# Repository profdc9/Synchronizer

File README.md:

# Synchronizer

Keep a mechanical pendulum clock on time by disciplining it to NTP or GPS —
**without modifying the clock in any way.**

The device sits behind the clock. Two coils reach through the back of the
case: one listens to the pendulum, the other nudges it. Nothing is glued to
the bob, nothing is drilled, nothing is tapped into the movement. Take the
device away and you have an ordinary pendulum clock again.

## How it works

A pendulum clock keeps time by counting swings. If the pendulum runs a
little fast or slow — and they all do, with temperature, with the mainspring
unwinding, with the barometric pressure — the hands drift. The usual fix is
to adjust the rating nut and accept a few seconds a day.

This device measures the pendulum against an accurate reference and gives it
a very small push, at the right moment, to hold it on time.

### Sensing the pendulum

The **sense coil** is an air-cored coil of many turns. It sits behind the
case, near one end of the pendulum's travel, and forms a parallel resonant
tank with C3 (in parallel with C4, an optional trim position). The firmware
drives that tank at its resonant frequency with a square wave.

When the bob swings past, it changes the coil's inductance and loads it with
eddy-current loss. Either way the tank is pulled off resonance, its
impedance falls, and the voltage across it drops. An LM358 amplifies that,
and the result is read two ways: as the raw waveform, and through an
envelope detector that turns it into a slow bump. The bump is the bob going
past.

Arrival time is taken as the **midpoint between the two threshold
crossings**, not the peak. At the end of its travel the bob is nearly
stationary, so the bump is broad and its peak is poorly localised — but the
two flanks are steep and symmetric about the turning point.

### Nudging the pendulum

The **drive coil** is wound on a soft iron core and sits at the other end of
the swing. Energising it attracts the bob's steel backing. It can only pull,
never push, so correction is entirely a matter of *when*:

- pulse **just before** the bob arrives → it gets there sooner → **the clock
  advances**
- pulse **just after** it turns and starts back → it is held a moment
  longer → **the clock retards**

The pushes needed are tiny. On the development clock, correcting 11 s/day
works out to about **113 microseconds of retard per swing** — far too little
to deliver as a pulse every swing. So the firmware accumulates the demand
and spends it whole: one short pulse every few dozen swings.

### Keeping time

A Raspberry Pi Pico W runs the whole thing, and serves a web interface for
everything else — status, calibration, tuning. Setting one up needs no
serial terminal and no app: a board with no network raises its own access
point, and joining it opens the setup form. Afterwards it answers at
`synchronizer.local` and advertises itself over DNS-SD, so there is no IP
address to hunt for. The page carries a console that runs the same command
line as the serial port, and the same thing is reachable from `curl` for
scripting or remote debugging.

It gets the time over Wi-Fi by NTP, and keeps a model of UTC that NTP
corrects in both phase *and* rate —
the RP2040's crystal is only good to around 30 ppm, which is 2.6 s/day, a
sizeable fraction of the error being removed. A GPS receiver can be wired to
the expansion header later.

## The hardware

A single board, 99 × 62 mm, all through-hole parts. It is deliberately
**single-sided** — every track is on the bottom copper, with no vias and no
jumpers — so it can be milled at home if need be, though the boards in the
photo were commercially made.

### Connections

| | |
|---|---|
| **J1** | +12 V input, screw terminal |
| **J4** | +12 V input, barrel jack (wired in parallel with J1) |
| **J3** | Sense coil, screw terminal |
| **J5** | Drive coil, screw terminal |
| **J2** | 14-pin expansion header |

J2 carries GPIO5–GPIO15 with three grounds, for a GPS receiver or anything
else. GPIO12 and GPIO13 are UART0 TX/RX, on pins 10 and 11.

### Circuit blocks

**Power.** 12 V in, a 7805 down to 5 V, then a 1N5819 Schottky (D1) feeding
the Pico's VBUS and the LM358's supply. The diode is what lets you plug in
USB without back-feeding the regulator.

**Tank drive.** GPIO2 → Q1 (2N3904) → Q2 (2N3906), which injects into the
sense tank through R5 from the 12 V rail. A square wave at resonance.

**Amplifier.** Two inverting LM358 stages, both with 100 kΩ feedback,
biased to about 1.5 V so they run from a single supply. The op-amp is
socketed.

The first stage is fed from the tank through C6, only 100 pF, so its
reactance — roughly 80 kΩ at 20 kHz — dominates the 10 kΩ input resistor.
That makes the stage a gentle high-pass of about ×1.3 at 20 kHz rising with
frequency, rather than a flat ×10. C6 is a light tap on the tank rather than
a load on it, and it also adds its own 100 pF to the tank's capacitance
alongside C3. The second stage is AC-coupled through C8 and does run at
about ×10.

**Detectors.** The amplified waveform goes to ADC1 through R20. It also goes
through R19 and C11 into a clamp-and-rectify envelope detector (D3, D4) with
C9 and R21 setting the decay, and that goes to ADC0. D7 and D8 clamp both
ADC inputs to 3V3; D5, D6 and D9 clamp the tank input.

**Drive.** GPIO4 → Q4 (2N3904) → pulls the gate of Q3, an IRF9540N P-channel
MOSFET, whose source sits on +12 V. **GPIO4 high energises the coil.** The
current runs through R6, a 10 Ω power resistor. D2 (UF4007) is the flyback
clamp across the coil, and R22 with C10 snubs the switching node. R17 and
R18 are unpopulated positions for damping the coils if you need it.

**R6's job is damping the drive circuit's oscillations, not setting a
current limit by design** — size it to the coil actually wound rather than
assuming the populated value. A lower-resistance coil wants a smaller R6, and
in many cases R6 can be 0 Ω outright; a higher-resistance coil can tolerate,
and may need, more damping.

> **A word of caution about R6.** The coil's DC resistance depends on what
> you wind, and R6 is in series with it across 12 V. A pulse left on could
> put several watts into that resistor. The firmware bounds every pulse
> three independent ways — a hard ceiling on width, a watchdog timer that
> drops the pin regardless of what the rest of the code believes, and a
> token bucket capping the long-run duty cycle — and the pin is driven low
> before anything else initialises. Keep those limits in mind before
> widening the default pulse.

### Pin assignments

| Signal | Pico | Function |
|---|---|---|
| `/OSCIL` | GPIO2 | tank drive, square wave at resonance |
| `/PULSE` | GPIO4 | drive coil; **high = coil energised** |
| `/AMPLITUDE` | GPIO26 / ADC0 | envelope detector output |
| `/OSC_SIGNAL` | GPIO27 / ADC1 | amplified tank waveform |

## Physical setup

<table>
<tr>
<td width="50%"></td>
<td width="50%"></td>
</tr>
<tr>
<td>The development clock — a 31-day mantel regulator. Neither coil touches
it; both stand free behind the case, reaching through the back wall.</td>
<td>The two coil holders assembled and wired to the board, placed at
opposite extremes of the pendulum's swing — the recommended default
geometry. Each stands on a 3D-printed platform with a ballast cup at its
base — filled here with cement — so it stays put on the shelf rather than
picking up the pendulum's own vibration.</td>
</tr>
<tr>
<td></td>
<td></td>
</tr>
<tr>
<td>The drive coil: a 50 mm × 35 mm, 500 N lifting electromagnet, 12 V at
about 250 mA, on its holder.</td>
<td>The sense coil, wound on its own form — the parallel resonant tank
described above.</td>
</tr>
</table>

Both holders are FreeCAD models, parametric in coil/magnet dimensions — see
`CAD/` below.

## The web interface

The device serves its own dashboard — no app, no cloud account, nothing to
install. These are from the clock above, running live.

At-a-glance status: the loop's lock state and uncorrected error, the clock's
measured swing rate, network and NTP health, the sense detector, and the
drive coil's per-direction pulse widths — all on one screen, live.

The uncorrected error over time, with advance and retard pulses marked where
they fired; the size of each NTP correction below it; and the chime
diagnostic showing what the hands should currently read.

The same command line as the serial port, in the browser — `STATUS` shown
here, but any command works, from `curl` or from this console.

## Repository layout

| | |
|---|---|
| `board/` | KiCad 7 project — schematic, PCB, gerbers, and a pcb2gcode setup for milling |
| `Code/synchronizer/` | Pico W firmware. See [its README](Code/synchronizer/README.md) for build and bring-up. |
| `CAD/` | FreeCAD models, parametric, plus their STLs. See [its README](CAD/README.md) for what each one is. |
| `Simulations/` | Qucs-S / ngspice models of the coil sensor and the coil pulser |

## Status

The board is built, the firmware runs the loop against the real clock shown
above, and it locks and holds it on time. Correction uses **KICK**: a
one-directional bang-bang scheme, no up-front gain measurement needed — it
fires a short pulse no more than once every few swings, only while the
error is on the side of zero that direction corrects, and stops once it
crosses back. An earlier design spent an accumulated phase error against a
measured "price per pulse" (`MEASURE`/`AUTH`); that path has been removed —
KICK needs no such calibration and has proven to be the simpler, working
approach.

Bring-up order, and the web interface, are in the
[firmware README](Code/synchronizer/README.md).

## Other clocks

Nothing in the firmware assumes a particular movement. Pendulum period,
escapement, gear ratio, coil placement and detector timing are all
configurable and stored in flash. The defaults describe the clock this was
developed against, and are only a starting point.

That clock is a 31-day wall clock about 40 cm tall. Measured from a
three-minute recording of its escapement:

- full swing period **0.857030 s** — nominally 6/7 s
- **8400 beats/hour**, 140 beats/min, **4200 full swings/hour**
- pendulum about **18.3 cm**
- runs roughly **11 s/day fast**
- **203 ms out of beat**, stably — the escapement releases at 0.678 of peak
  swing, where the bob still has 73% of its top speed, so it runs happily
  that way

Note that the bob only reaches each end of its travel once per full period,
so a coil at one extreme sees it 4200 times an hour, not 8400.

## Licence

The board carries **CC BY-SA 4.0** on its silkscreen, and the CAD models are
under the same licence; the full text is in
[`LICENSE-CC-BY-SA-4.0.txt`](LICENSE-CC-BY-SA-4.0.txt). The firmware sources
each carry a zlib-style permissive notice, and the full text is in
[`Code/synchronizer/LICENSE`](Code/synchronizer/LICENSE).

Daniel Marks

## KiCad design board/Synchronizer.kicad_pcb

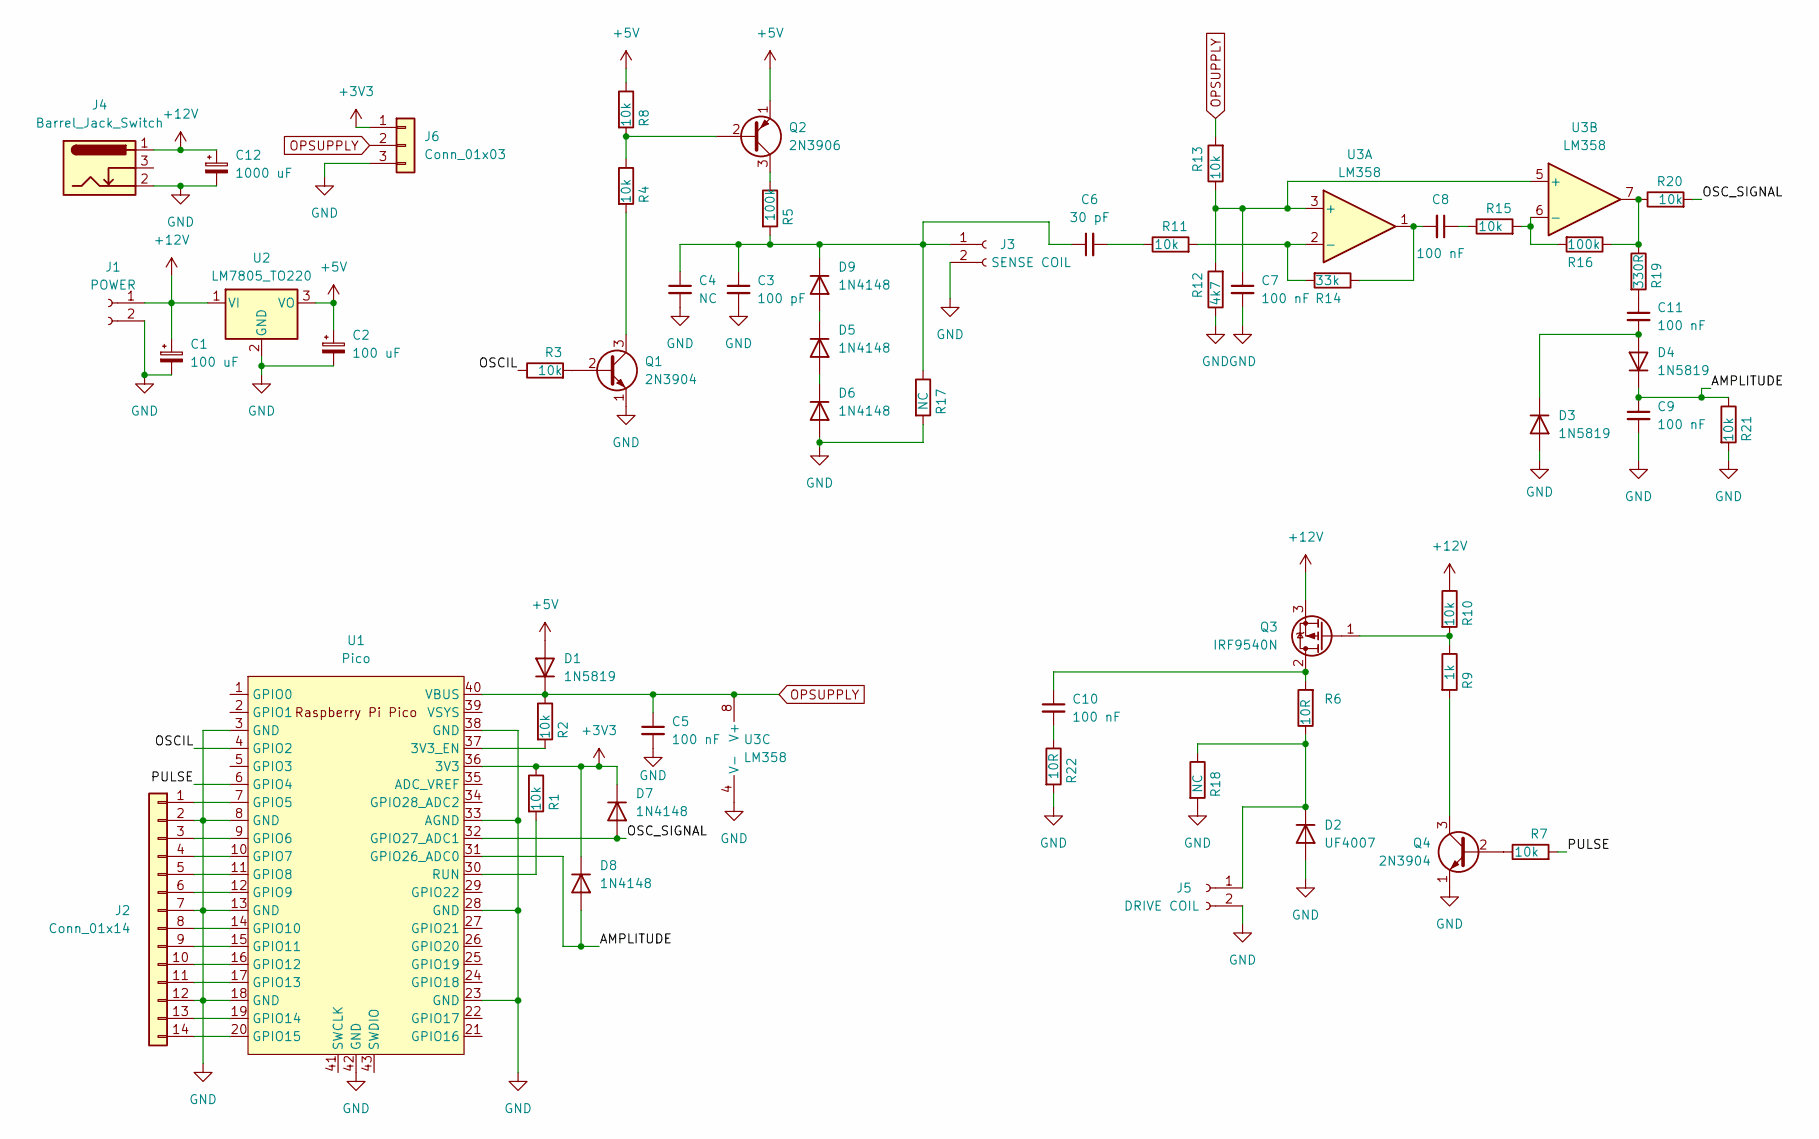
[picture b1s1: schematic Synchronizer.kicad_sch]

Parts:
C1, C2: 100 uF; CP_Radial_D5.0mm_P2.00mm
C3: 100 pF; C_Disc_D5.0mm_W2.5mm_P5.00mm
C4: NC; C_Disc_D5.0mm_W2.5mm_P5.00mm
C5, C7, C8, C9, C11: 100 nF; C_Disc_D5.0mm_W2.5mm_P5.00mm
C6: 30 pF; C_Disc_D5.0mm_W2.5mm_P5.00mm
C10: 100 nF; C_Rect_L7.0mm_W2.5mm_P5.00mm
C12: 1000 uF; CP_Radial_D8.0mm_P2.50mm
D1: 1N5819; D_DO-41_SOD81_P12.70mm_Horizontal
D2: UF4007; D_DO-41_SOD81_P7.62mm_Horizontal
D3, D4: 1N5819; D_DO-41_SOD81_P7.62mm_Horizontal
D5, D6, D7, D8, D9: 1N4148; D_DO-35_SOD27_P7.62mm_Horizontal
J1: POWER; TerminalBlock_bornier-2_P5.08mm
J2: Conn_01x14; PinHeader_1x14_P2.54mm_Vertical
J3: SENSE COIL; TerminalBlock_bornier-2_P5.08mm
J4: Barrel_Jack_Switch; BarrelJack_Horizontal
J5: DRIVE COIL; TerminalBlock_bornier-2_P5.08mm
J6: Conn_01x03; PinHeader_1x03_P2.54mm_Vertical
Q1, Q4: 2N3904; TO-92L_Inline_Wide
Q2: 2N3906; TO-92L_Inline_Wide
Q3: IRF9540N; TO-220-3_Vertical
R1, R2, R4, R8, R10, R13, R15, R20, R21: 10k; R_Axial_DIN0207_L6.3mm_D2.5mm_P7.62mm_Horizontal
R3, R7: 10k; R_Axial_DIN0207_L6.3mm_D2.5mm_P15.24mm_Horizontal
R5, R16: 100k; R_Axial_DIN0207_L6.3mm_D2.5mm_P7.62mm_Horizontal
R6: 10R; R_Axial_DIN0614_L14.3mm_D5.7mm_P15.24mm_Horizontal
R9: 1k; R_Axial_DIN0207_L6.3mm_D2.5mm_P7.62mm_Horizontal
R11: 10k; R_Axial_DIN0207_L6.3mm_D2.5mm_P10.16mm_Horizontal
R12: 4k7; R_Axial_DIN0207_L6.3mm_D2.5mm_P7.62mm_Horizontal
R14: 33k; R_Axial_DIN0207_L6.3mm_D2.5mm_P7.62mm_Horizontal
R17, R18: NC; R_Axial_DIN0207_L6.3mm_D2.5mm_P7.62mm_Horizontal
R19: 330R; R_Axial_DIN0207_L6.3mm_D2.5mm_P7.62mm_Horizontal
R22: 10R; R_Axial_DIN0207_L6.3mm_D2.5mm_P7.62mm_Horizontal
U1: Pico; RPi_Pico_SMD_TH
U2: LM7805_TO220; TO-220-3_Vertical
U3: LM358; DIP-8_W7.62mm_Socket

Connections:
+3V3: D7.1 (K), D8.1 (K), J6.1, R1.1, U1.36 (3V3)
+5V: C2.1, D1.2 (A), Q2.1 (E), R8.1, U2.3 (VO)
+12V: C1.1, C12.1, J1.1, J4.1, Q3.3 (S), R10.1, U2.1 (VI)
/AMPLITUDE: C9.1, D4.1 (K), D8.2 (A), R21.1, U1.31 (GPIO26_ADC0)
/OSCIL: R3.1, U1.4 (GPIO2)
/OSC_SIGNAL: D7.2 (A), R20.2, U1.32 (GPIO27_ADC1)
/PULSE: R7.2, U1.6 (GPIO4)
GND: C1.2, C2.2, C3.2, C4.2, C5.2, C7.2, C9.2, C12.2, D2.2 (A), D3.2 (A), D6.2 (A), J1.2, J2.2, J2.7, J2.12, J3.2, J4.2, J5.2, J6.3, Q1.1 (E), Q4.1 (E), R12.1, R17.2, R18.2, R21.2, R22.2, U1.3 (GND), U1.8 (GND), U1.13 (GND), U1.18 (GND), U1.23 (GND), U1.28 (GND), U1.33 (AGND), U1.38 (GND), U1.42 (GND), U2.2 (GND), U3.4 (V-)
unnamed: C6.2, R11.1
unnamed: C8.1, R15.1
unnamed: C8.2, R14.1, U3.1
unnamed: C10.2, R22.1
unnamed: C11.1, R19.2
unnamed: D2.1 (K), J5.1, R6.1, R18.1
unnamed: C11.2, D3.1 (K), D4.2 (A)
unnamed: D5.2 (A), D6.1 (K)
unnamed: D5.1 (K), D9.2 (A)
unnamed: C3.1, C4.1, C6.1, D9.1 (K), J3.1, R5.2, R17.1
unnamed: J2.1, U1.7 (GPIO5)
unnamed: J2.3, U1.9 (GPIO6)
unnamed: J2.4, U1.10 (GPIO7)
unnamed: J2.5, U1.11 (GPIO8)
unnamed: J2.6, U1.12 (GPIO9)
unnamed: J2.8, U1.14 (GPIO10)
unnamed: J2.9, U1.15 (GPIO11)
unnamed: J2.10, U1.16 (GPIO12)
unnamed: J2.11, U1.17 (GPIO13)
unnamed: J2.13, U1.19 (GPIO14)
unnamed: J2.14, U1.20 (GPIO15)
unnamed: Q1.2 (B), R3.2
unnamed: Q1.3 (C), R4.2
unnamed: Q2.2 (B), R4.1, R8.2
unnamed: Q2.3 (C), R5.1
unnamed: C10.1, Q3.2 (D), R6.2
unnamed: Q3.1 (G), R9.1, R10.2
unnamed: Q4.2 (B), R7.1
unnamed: Q4.3 (C), R9.2
unnamed: R16.1, R19.1, R20.1, U3.7
unnamed: R2.2, U1.37 (3V3_EN)
unnamed: R1.2, U1.30 (RUN)
unnamed: C7.1, R12.2, R13.1, U3.3 (+), U3.5 (+)
unnamed: R11.2, R14.2, U3.2 (-)
unnamed: R15.2, R16.2, U3.6 (-)
OPSUPPLY: C5.1, D1.1 (K), J6.2, R2.1, R13.2, U1.40 (VBUS), U3.8 (V+)

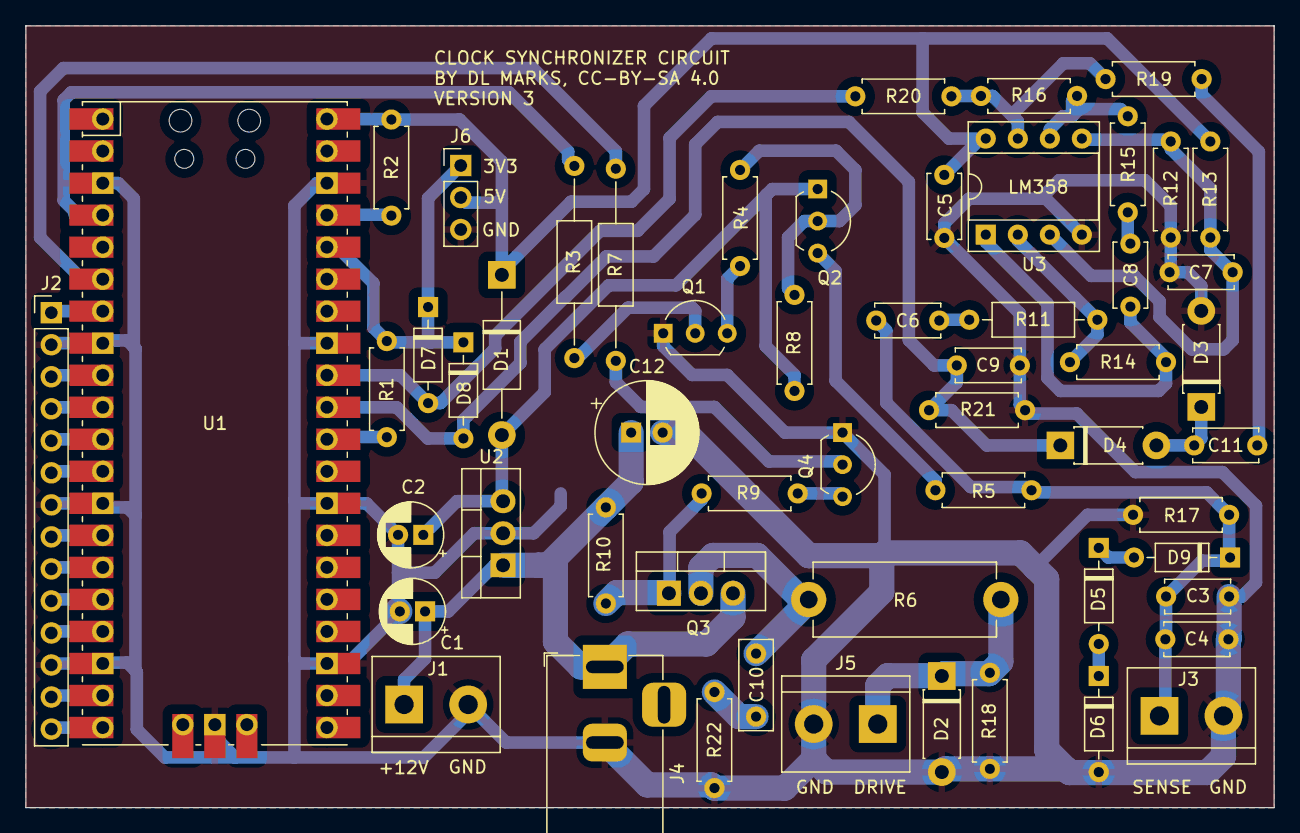
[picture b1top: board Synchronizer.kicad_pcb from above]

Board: 2 copper layers, 99.0 x 62.0 mm, 56 parts (0 on the bottom side), 44 nets.

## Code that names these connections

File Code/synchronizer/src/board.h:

/* board.h - pin map and fixed constants for the Synchronizer board

   Every pin here is taken from board/Synchronizer.kicad_sch (net names in
   brackets).  Do not change these without changing the PCB.
*/

/*
   Copyright (c) 2026 Daniel Marks

  This software is provided 'as-is', without any express or implied
  warranty. In no event will the authors be held liable for any damages
  arising from the use of this software.

  Permission is granted to anyone to use this software for any purpose,
  including commercial applications, and to alter it and redistribute it
  freely, subject to the following restrictions:

  1. The origin of this software must not be misrepresented; you must not
   claim that you wrote the original software. If you use this software
   in a product, an acknowledgment in the product documentation would be
   appreciated but is not required.
  2. Altered source versions must be plainly marked as such, and must not be
   misrepresented as being the original software.
  3. This notice may not be removed or altered from any source distribution.
*/

#ifndef _BOARD_H
#define _BOARD_H

#ifdef __cplusplus
extern "C" {
#endif

/* --- sense side ------------------------------------------------------- */

/* [/OSCIL] GPIO2 -> R3 -> Q1 (2N3904) -> R4 -> Q2 (2N3906) -> R5 -> tank.
   Driving this square wave at the tank's resonance excites the parallel
   LC formed by the sense coil (J3) and C3 || C4. */
#define GPIO_OSCIL          2

/* [/AMPLITUDE] GPIO26 / ADC0.  Envelope detector (R19, C11, D3, D4, R21, C9)
   fed from the LM358 second stage.  This is the slow control-path signal. */
#define GPIO_AMPLITUDE      26
#define ADC_CH_AMPLITUDE    0

/* [/OSC_SIGNAL] GPIO27 / ADC1.  The amplified tank waveform itself, before
   envelope detection.  Diagnostics only - it needs a fast capture. */
#define GPIO_OSC_SIGNAL     27
#define ADC_CH_OSC_SIGNAL   1

/* --- drive side ------------------------------------------------------- */

/* [/PULSE] GPIO4 -> R7 -> Q4 (2N3904) -> R9 -> gate of Q3 (IRF9540N, P-ch).
   Q4 on pulls the gate toward ground, VGS = -12 V, the FET conducts.
   So: GPIO4 HIGH energises the drive coil on J5.  It must idle LOW.

   The coil current runs through R6 (10R).  With an unknown coil resistance
   that resistor can be asked to dissipate several watts, so every pulse is
   bounded in both width and duty cycle - see drive.h. */
#define GPIO_PULSE          4

/* --- expansion -------------------------------------------------------- */

/* J2 carries GPIO5..GPIO15 for the GPS receiver that may be added later.
   GPIO12/GPIO13 are UART0 TX/RX (J2 pins 10 and 11). */
#define GPIO_GPS_TX         12
#define GPIO_GPS_RX         13
#define GPS_UART            uart0

/* --- the clock ---------------------------------------------------------

   DEFAULTS ONLY.  Nothing in this firmware may assume a particular
   movement: pendulum period, escapement, bob material and coil placement
   all vary from clock to clock, and every one of them is configurable and
   stored in flash.  These values seed a fresh configuration and describe
   the clock the firmware was developed against, nothing more.

   That clock: measured from a three-minute recording of the escapement on
   2026-09-10, the pattern repeats every 0.857030 s, which is 8400 beats
   per hour within the measurement error - 4200 full swings/hour,
   100800/day.

   beats_per_period is 2 for an anchor, deadbeat or pin-pallet escapement:
   two pallets, one tooth released per half period. */
#define DEFAULT_BEATS_PER_HOUR   8400u
#define DEFAULT_BEATS_PER_PERIOD 2u

#ifdef __cplusplus
}
#endif

#endif /* _BOARD_H */

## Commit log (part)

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2025-10-10 first committ
2025-10-11 Added pcb2gcode generation of gcode for mill
2025-10-11 Added CAD of coil form
2025-10-15 added extra gpio pins
2025-10-22 redo drawing
2026-06-04 where I left off
2026-06-06 separate coils
2026-06-21 Fixed two unconnected traces

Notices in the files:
board/Synchronizer.kicad_pcb:
BY DL MARKS, CC-BY-SA 4.0
